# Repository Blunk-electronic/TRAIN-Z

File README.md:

# TRAIN-Z
A open hardware and software embedded Z80 computer
Please find more colorful details at
http://www.blunk-electronic.de/train-z/

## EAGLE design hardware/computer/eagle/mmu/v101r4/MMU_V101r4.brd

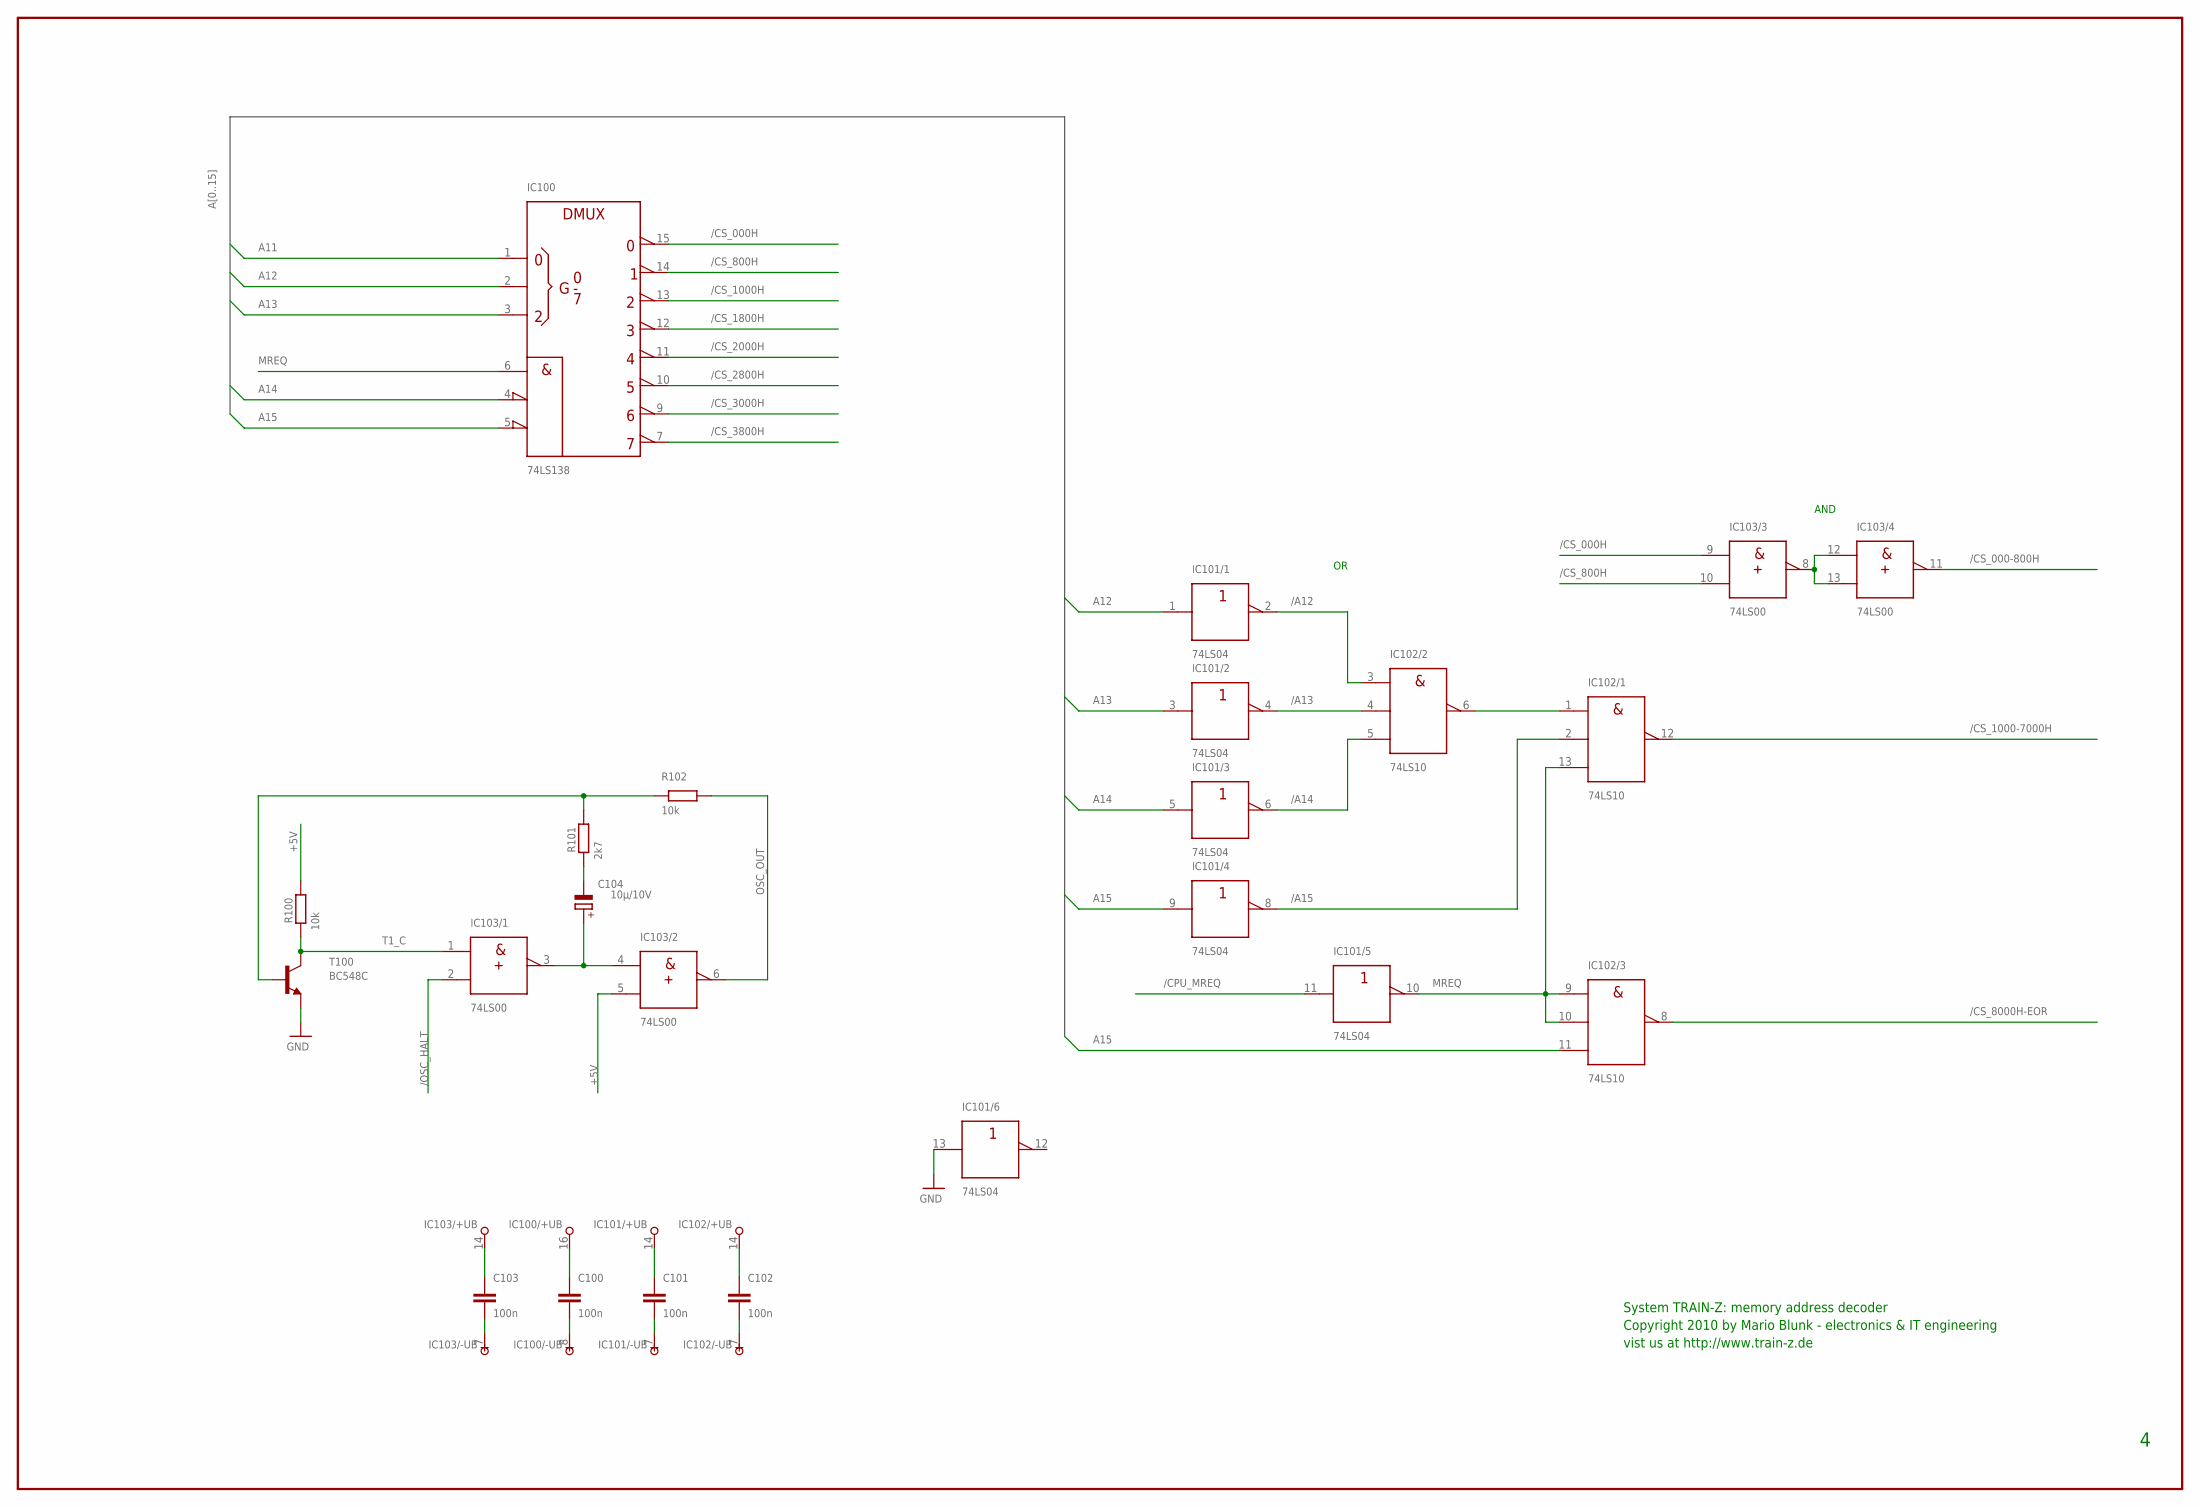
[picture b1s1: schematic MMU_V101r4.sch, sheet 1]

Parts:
C100, C101, C102, C103: 100n; C050-030X075
C104: 10µ/10V; E2,5-7
IC100: 74LS138; DIL16
IC101: 74LS04; DIL14
IC102: 74LS10; DIL14
IC103: 74LS00; DIL14
R100, R102: 10k; 0207/10
R101: 2k7; 0207/10
T100: BC548C; TO92

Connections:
+5V: C100.1, C101.1, C102.1, C103.1, IC100.16 (+UB), IC101.14 (+UB), IC102.14 (+UB), IC103.5 (B), IC103.14 (+UB), R100.2; also elsewhere on the board
/A12: IC101.2 (Y), IC102.3 (A)
/A13: IC101.4 (Y), IC102.4 (B)
/A14: IC101.6 (Y), IC102.5 (C)
/A15: IC101.8 (Y), IC102.2 (B)
/CPU_MREQ: IC101.11 (A); also elsewhere on the board
/CS_000-800H: IC103.11 (Y); also elsewhere on the board
/CS_000H: IC100.15 (Y0), IC103.9 (A)
/CS_800H: IC100.14 (Y1), IC103.10 (B)
/CS_1000-7000H: IC102.12 (Y); also elsewhere on the board
/CS_1000H: IC100.13 (Y2)
/CS_1800H: IC100.12 (Y3)
/CS_2000H: IC100.11 (Y4)
/CS_2800H: IC100.10 (Y5)
/CS_3000H: IC100.9 (Y6)
/CS_3800H: IC100.7 (Y7)
/CS_8000H-EOR: IC102.8 (Y); also elsewhere on the board
/OSC_HALT: IC103.2 (B); also elsewhere on the board
A11: IC100.1 (A); also elsewhere on the board
A12: IC100.2 (B), IC101.1 (A); also elsewhere on the board
A12ORA13ORA14: IC102.1 (A), IC102.6 (Y)
A13: IC100.3 (C), IC101.3 (A); also elsewhere on the board
A14: IC100.4 (!G2A), IC101.5 (A); also elsewhere on the board
A15: IC100.5 (!G2B), IC101.9 (A), IC102.11 (C); also elsewhere on the board
C14+: C104.+, IC103.3 (Y), IC103.4 (A)
C14-: C104.-, R101.1
CS_000-800H: IC103.8 (Y), IC103.12 (A), IC103.13 (B)
GND: C100.2, C101.2, C102.2, C103.2, IC100.8 (-UB), IC101.7 (-UB), IC101.13 (A), IC102.7 (-UB), IC103.7 (-UB), T100.1 (E); also elsewhere on the board
MREQ: IC100.6 (G1), IC101.10 (Y), IC102.9 (A), IC102.10 (B), IC102.13 (C)
OSC_OUT: IC103.6 (Y), R102.2; also elsewhere on the board
T1_B: R101.2, R102.1, T100.2 (B)
T1_C: IC103.1 (A), R100.1, T100.3 (C)

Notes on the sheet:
AND
System TRAIN-Z: memory address decoder
Copyright 2010 by Mario Blunk - electronics & IT engineering
vist us at http://www.train-z.de

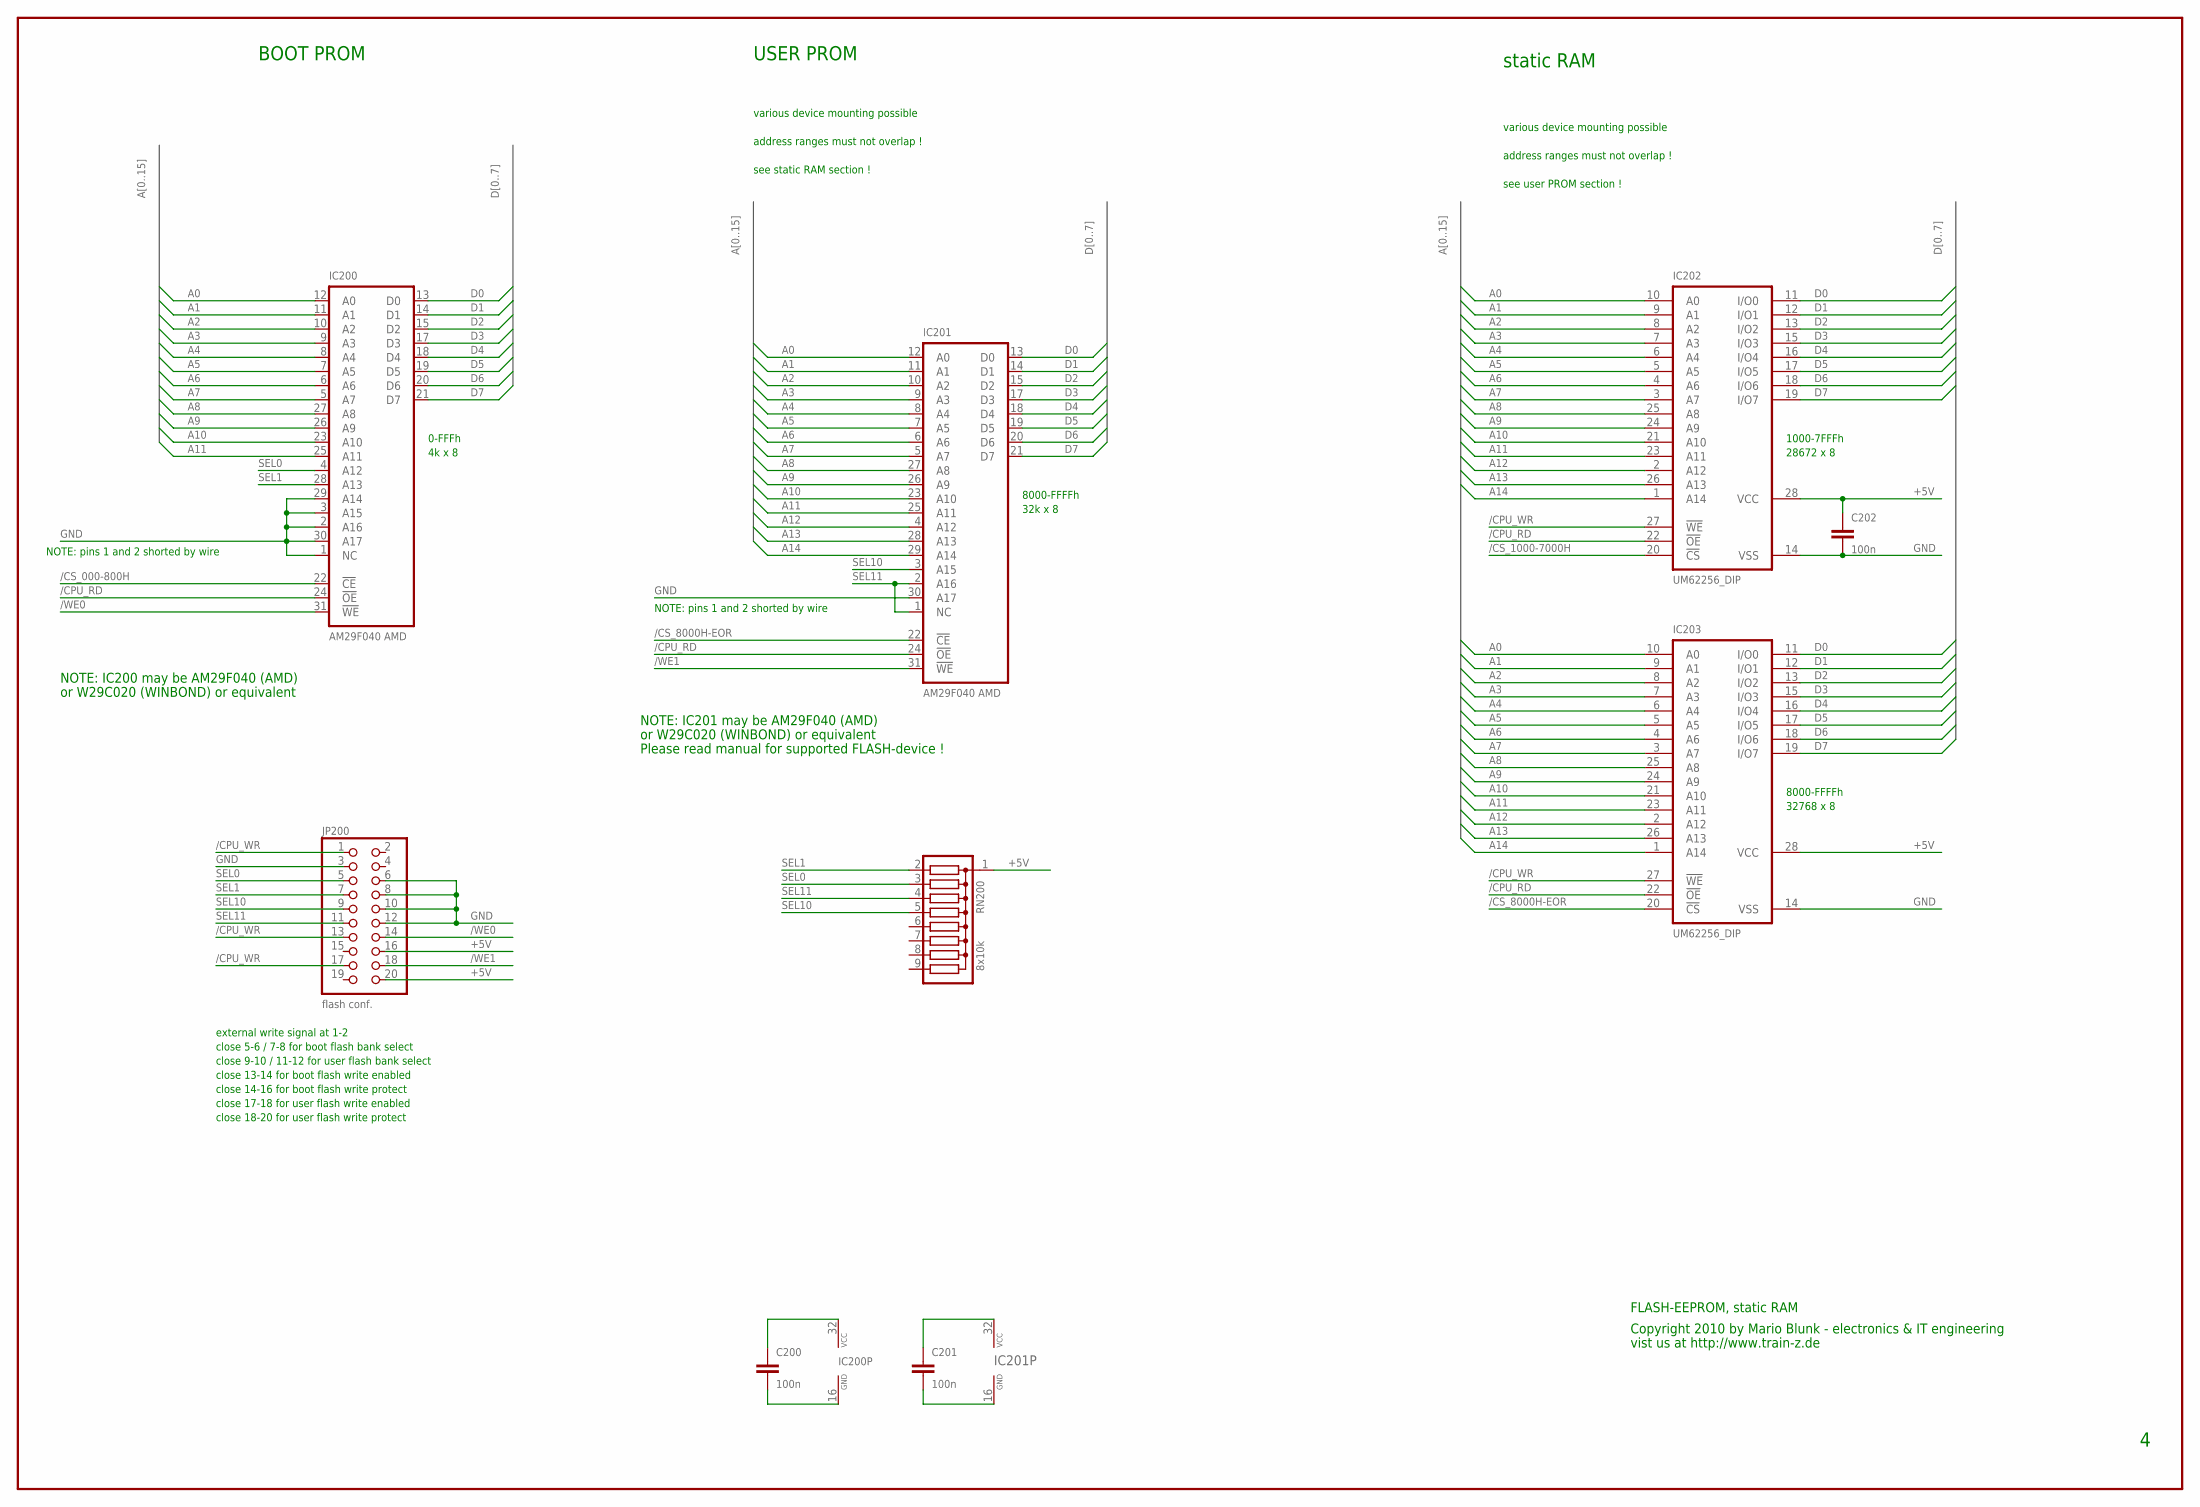
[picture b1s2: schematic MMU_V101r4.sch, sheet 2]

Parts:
C200, C201, C202: 100n; C050-030X075
IC200, IC201: AM29F040 AMD; DIL32
IC202, IC203: UM62256_DIP; DIL28-6
JP200: flash conf.; 2X10
RN200: 8x10k; SIL9

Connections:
+5V: C200.1, C201.1, C202.1, IC200.32 (VCC), IC201.32 (VCC), IC202.28 (VCC), IC203.28 (VCC), JP200.16, JP200.20, RN200.1; also elsewhere on the board
/CPU_RD: IC200.24 (!OE), IC201.24 (!OE), IC202.22 (!OE), IC203.22 (!OE); also elsewhere on the board
/CPU_WR: IC202.27 (!WE), IC203.27 (!WE), JP200.1, JP200.13, JP200.17; also elsewhere on the board
/CS_000-800H: IC200.22 (!CE); also elsewhere on the board
/CS_1000-7000H: IC202.20 (!CS); also elsewhere on the board
/CS_8000H-EOR: IC201.22 (!CE), IC203.20 (!CS); also elsewhere on the board
/WE0: IC200.31 (!WE), JP200.14
/WE1: IC201.31 (!WE), JP200.18
A0: IC200.12 (A0), IC201.12 (A0), IC202.10 (A0), IC203.10 (A0); also elsewhere on the board
A1: IC200.11 (A1), IC201.11 (A1), IC202.9 (A1), IC203.9 (A1); also elsewhere on the board
A2: IC200.10 (A2), IC201.10 (A2), IC202.8 (A2), IC203.8 (A2); also elsewhere on the board
A3: IC200.9 (A3), IC201.9 (A3), IC202.7 (A3), IC203.7 (A3); also elsewhere on the board
A4: IC200.8 (A4), IC201.8 (A4), IC202.6 (A4), IC203.6 (A4); also elsewhere on the board
A5: IC200.7 (A5), IC201.7 (A5), IC202.5 (A5), IC203.5 (A5); also elsewhere on the board
A6: IC200.6 (A6), IC201.6 (A6), IC202.4 (A6), IC203.4 (A6); also elsewhere on the board
A7: IC200.5 (A7), IC201.5 (A7), IC202.3 (A7), IC203.3 (A7); also elsewhere on the board
A8: IC200.27 (A8), IC201.27 (A8), IC202.25 (A8), IC203.25 (A8); also elsewhere on the board
A9: IC200.26 (A9), IC201.26 (A9), IC202.24 (A9), IC203.24 (A9); also elsewhere on the board
A10: IC200.23 (A10), IC201.23 (A10), IC202.21 (A10), IC203.21 (A10); also elsewhere on the board
A11: IC200.25 (A11), IC201.25 (A11), IC202.23 (A11), IC203.23 (A11); also elsewhere on the board
A12: IC201.4 (A12), IC202.2 (A12), IC203.2 (A12); also elsewhere on the board
A13: IC201.28 (A13), IC202.26 (A13), IC203.26 (A13); also elsewhere on the board
A14: IC201.29 (A14), IC202.1 (A14), IC203.1 (A14); also elsewhere on the board
D0: IC200.13 (D0), IC201.13 (D0), IC202.11 (I/O0), IC203.11 (I/O0); also elsewhere on the board
D1: IC200.14 (D1), IC201.14 (D1), IC202.12 (I/O1), IC203.12 (I/O1); also elsewhere on the board
D2: IC200.15 (D2), IC201.15 (D2), IC202.13 (I/O2), IC203.13 (I/O2); also elsewhere on the board
D3: IC200.17 (D3), IC201.17 (D3), IC202.15 (I/O3), IC203.15 (I/O3); also elsewhere on the board
D4: IC200.18 (D4), IC201.18 (D4), IC202.16 (I/O4), IC203.16 (I/O4); also elsewhere on the board
D5: IC200.19 (D5), IC201.19 (D5), IC202.17 (I/O5), IC203.17 (I/O5); also elsewhere on the board
D6: IC200.20 (D6), IC201.20 (D6), IC202.18 (I/O6), IC203.18 (I/O6); also elsewhere on the board
D7: IC200.21 (D7), IC201.21 (D7), IC202.19 (I/O7), IC203.19 (I/O7); also elsewhere on the board
GND: C200.2, C201.2, C202.2, IC200.1 (NC), IC200.2 (A16), IC200.3 (A15), IC200.16 (GND), IC200.29 (A14), IC200.30 (A17), IC201.16 (GND), IC201.30 (A17), IC202.14 (VSS), IC203.14 (VSS), JP200.3, JP200.6, JP200.8, JP200.10, JP200.12; also elsewhere on the board
SEL0: IC200.4 (A12), JP200.5, RN200.3
SEL1: IC200.28 (A13), JP200.7, RN200.2
SEL10: IC201.3 (A15), JP200.9, RN200.5
SEL11: IC201.1 (NC), IC201.2 (A16), JP200.11, RN200.4

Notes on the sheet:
0-FFFh
4k x 8
BOOT PROM
USER PROM
various device mounting possible
address ranges must not overlap !
see static RAM section !
FLASH-EEPROM, static RAM
close 9-10 / 11-12 for user flash bank select
8000-FFFFh
32k x 8
see user PROM section !
1000-7FFFh
28672 x 8
32768 x 8
close 5-6 / 7-8 for boot flash bank select
static RAM
external write signal at 1-2
close 13-14 for boot flash write enabled
close 14-16 for boot flash write protect
close 17-18 for user flash write enabled
close 18-20 for user flash write protect
NOTE: pins 1 and 2 shorted by wire
Please read manual for supported FLASH-device !
NOTE: IC200 may be AM29F040 (AMD)
or W29C020 (WINBOND) or equivalent
NOTE: IC201 may be AM29F040 (AMD)
Copyright 2010 by Mario Blunk - electronics & IT engineering
vist us at http://www.train-z.de

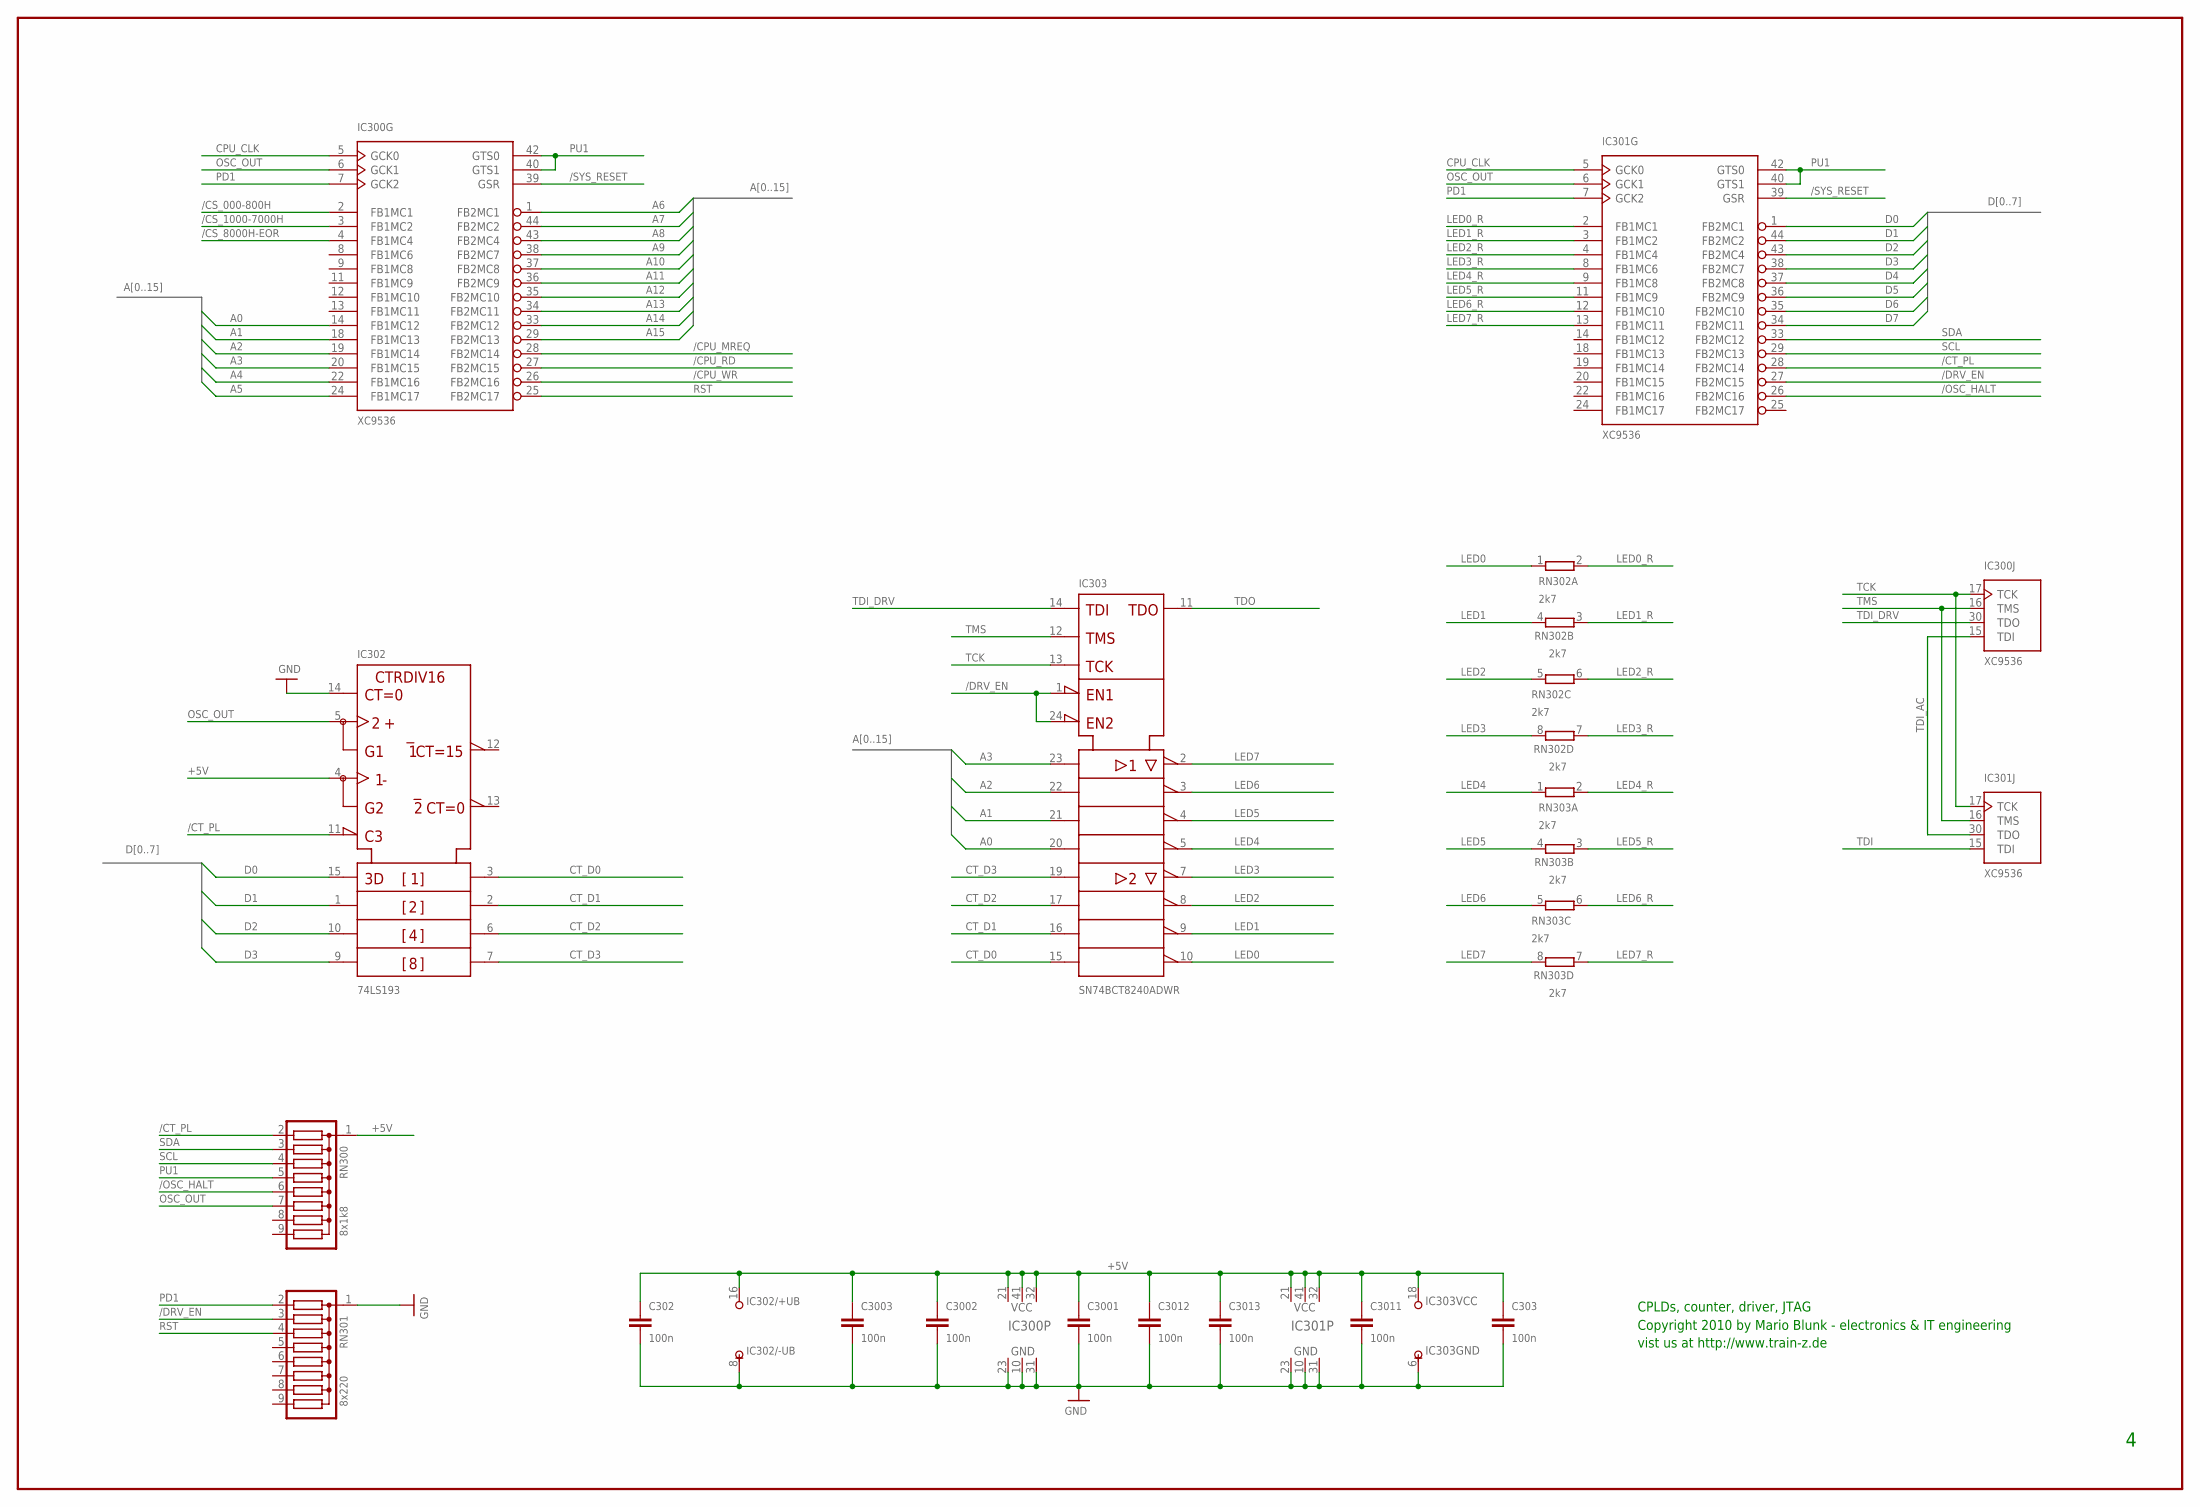
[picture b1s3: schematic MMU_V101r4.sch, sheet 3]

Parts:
C302: 100n; C050-025X075
C303, C3001, C3002, C3003, C3011, C3012, C3013: 100n; C050-030X075
IC300, IC301: XC9536; PLCC-S44
IC302: 74LS193; DIL16
IC303: SN74BCT8240ADWR; SOIC24
RN300: 8x1k8; SIL9
RN301: 8x220; SIL9
RN302, RN303: 2k7; SIL8

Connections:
+5V: C302.1, C303.1, C3001.1, C3002.1, C3003.1, C3011.1, C3012.1, C3013.1, IC300.21 (VCC), IC300.32 (VCC), IC300.41 (VCC), IC301.21 (VCC), IC301.32 (VCC), IC301.41 (VCC), IC302.4 (DOWN), IC302.16 (+UB), IC303.18 (+UB), RN300.1; also elsewhere on the board
/CPU_MREQ: IC300.28 (FB2MC14); also elsewhere on the board
/CPU_RD: IC300.27 (FB2MC15); also elsewhere on the board
/CPU_WR: IC300.26 (FB2MC16); also elsewhere on the board
/CS_000-800H: IC300.2 (FB1MC1); also elsewhere on the board
/CS_1000-7000H: IC300.3 (FB1MC2); also elsewhere on the board
/CS_8000H-EOR: IC300.4 (FB1MC4); also elsewhere on the board
/CT_PL: IC301.28 (FB2MC14), IC302.11 (!LOAD), RN300.2; also elsewhere on the board
/DRV_EN: IC301.27 (FB2MC15), IC303.1 (/EN1), IC303.24 (/EN2), RN301.3; also elsewhere on the board
/OSC_HALT: IC301.26 (FB2MC16), RN300.6; also elsewhere on the board
/SYS_RESET: IC300.39 (GSR), IC301.39 (GSR); also elsewhere on the board
A0: IC300.14 (FB1MC12), IC303.20 (A4); also elsewhere on the board
A1: IC300.18 (FB1MC13), IC303.21 (A3); also elsewhere on the board
A2: IC300.19 (FB1MC14), IC303.22 (A2); also elsewhere on the board
A3: IC300.20 (FB1MC15), IC303.23 (A1); also elsewhere on the board
A4: IC300.22 (FB1MC16); also elsewhere on the board
A5: IC300.24 (FB1MC17); also elsewhere on the board
A6: IC300.1 (FB2MC1); also elsewhere on the board
A7: IC300.44 (FB2MC2); also elsewhere on the board
A8: IC300.43 (FB2MC4); also elsewhere on the board
A9: IC300.38 (FB2MC7); also elsewhere on the board
A10: IC300.37 (FB2MC8); also elsewhere on the board
A11: IC300.36 (FB2MC9); also elsewhere on the board
A12: IC300.35 (FB2MC10); also elsewhere on the board
A13: IC300.34 (FB2MC11); also elsewhere on the board
A14: IC300.33 (FB2MC12); also elsewhere on the board
A15: IC300.29 (FB2MC13); also elsewhere on the board
CPU_CLK: IC300.5 (GCK0), IC301.5 (GCK0); also elsewhere on the board
CT_D0: IC302.3 (QA), IC303.15 (A8); also elsewhere on the board
CT_D1: IC302.2 (QB), IC303.16 (A7); also elsewhere on the board
CT_D2: IC302.6 (QC), IC303.17 (A6); also elsewhere on the board
CT_D3: IC302.7 (QD), IC303.19 (A5); also elsewhere on the board
D0: IC301.1 (FB2MC1), IC302.15 (A); also elsewhere on the board
D1: IC301.44 (FB2MC2), IC302.1 (B); also elsewhere on the board
D2: IC301.43 (FB2MC4), IC302.10 (C); also elsewhere on the board
D3: IC301.38 (FB2MC7), IC302.9 (D); also elsewhere on the board
D4: IC301.37 (FB2MC8); also elsewhere on the board
D5: IC301.36 (FB2MC9); also elsewhere on the board
D6: IC301.35 (FB2MC10); also elsewhere on the board
D7: IC301.34 (FB2MC11); also elsewhere on the board
GND: C302.2, C303.2, C3001.2, C3002.2, C3003.2, C3011.2, C3012.2, C3013.2, IC300.10 (GND), IC300.23 (GND), IC300.31 (GND), IC301.10 (GND), IC301.23 (GND), IC301.31 (GND), IC302.8 (-UB), IC302.14 (CLR), IC303.6 (-UB), RN301.1; also elsewhere on the board
LED0: IC303.10 (/Y8), RN302.1; also elsewhere on the board
LED0_R: IC301.2 (FB1MC1), RN302.2; also elsewhere on the board
LED1: IC303.9 (/Y7), RN302.4 (2); also elsewhere on the board
LED1_R: IC301.3 (FB1MC2), RN302.3 (1); also elsewhere on the board
LED2: IC303.8 (/Y6), RN302.5 (1); also elsewhere on the board
LED2_R: IC301.4 (FB1MC4), RN302.6 (2); also elsewhere on the board
LED3: IC303.7 (/Y5), RN302.8 (2); also elsewhere on the board
LED3_R: IC301.8 (FB1MC6), RN302.7 (1); also elsewhere on the board
LED4: IC303.5 (/Y4), RN303.1; also elsewhere on the board
LED4_R: IC301.9 (FB1MC8), RN303.2; also elsewhere on the board
LED5: IC303.4 (/Y3), RN303.4 (2); also elsewhere on the board
LED5_R: IC301.11 (FB1MC9), RN303.3 (1); also elsewhere on the board
LED6: IC303.3 (/Y2), RN303.5 (1); also elsewhere on the board
LED6_R: IC301.12 (FB1MC10), RN303.6 (2); also elsewhere on the board
LED7: IC303.2 (/Y1), RN303.8 (2); also elsewhere on the board
LED7_R: IC301.13 (FB1MC11), RN303.7 (1); also elsewhere on the board
OSC_OUT: IC300.6 (GCK1), IC301.6 (GCK1), IC302.5 (UP), RN300.7; also elsewhere on the board
PD1: IC300.7 (GCK2), IC301.7 (GCK2), RN301.2; also elsewhere on the board
PU1: IC300.40 (GTS1), IC300.42 (GTS0), IC301.40 (GTS1), IC301.42 (GTS0), RN300.5; also elsewhere on the board
RST: IC300.25 (FB2MC17), RN301.4; also elsewhere on the board
SCL: IC301.29 (FB2MC13), RN300.4; also elsewhere on the board
SDA: IC301.33 (FB2MC12), RN300.3; also elsewhere on the board
TCK: IC300.17 (TCK), IC301.17 (TCK), IC303.13 (TCK); also elsewhere on the board
TDI: IC301.15 (TDI); also elsewhere on the board
TDI_AC: IC300.15 (TDI), IC301.30 (TDO); also elsewhere on the board
TDI_DRV: IC300.30 (TDO), IC303.14 (TDI); also elsewhere on the board
TDO: IC303.11 (TDO); also elsewhere on the board
TMS: IC300.16 (TMS), IC301.16 (TMS), IC303.12 (TMS); also elsewhere on the board

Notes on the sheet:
CPLDs, counter, driver, JTAG
Copyright 2010 by Mario Blunk - electronics & IT engineering
vist us at http://www.train-z.de
